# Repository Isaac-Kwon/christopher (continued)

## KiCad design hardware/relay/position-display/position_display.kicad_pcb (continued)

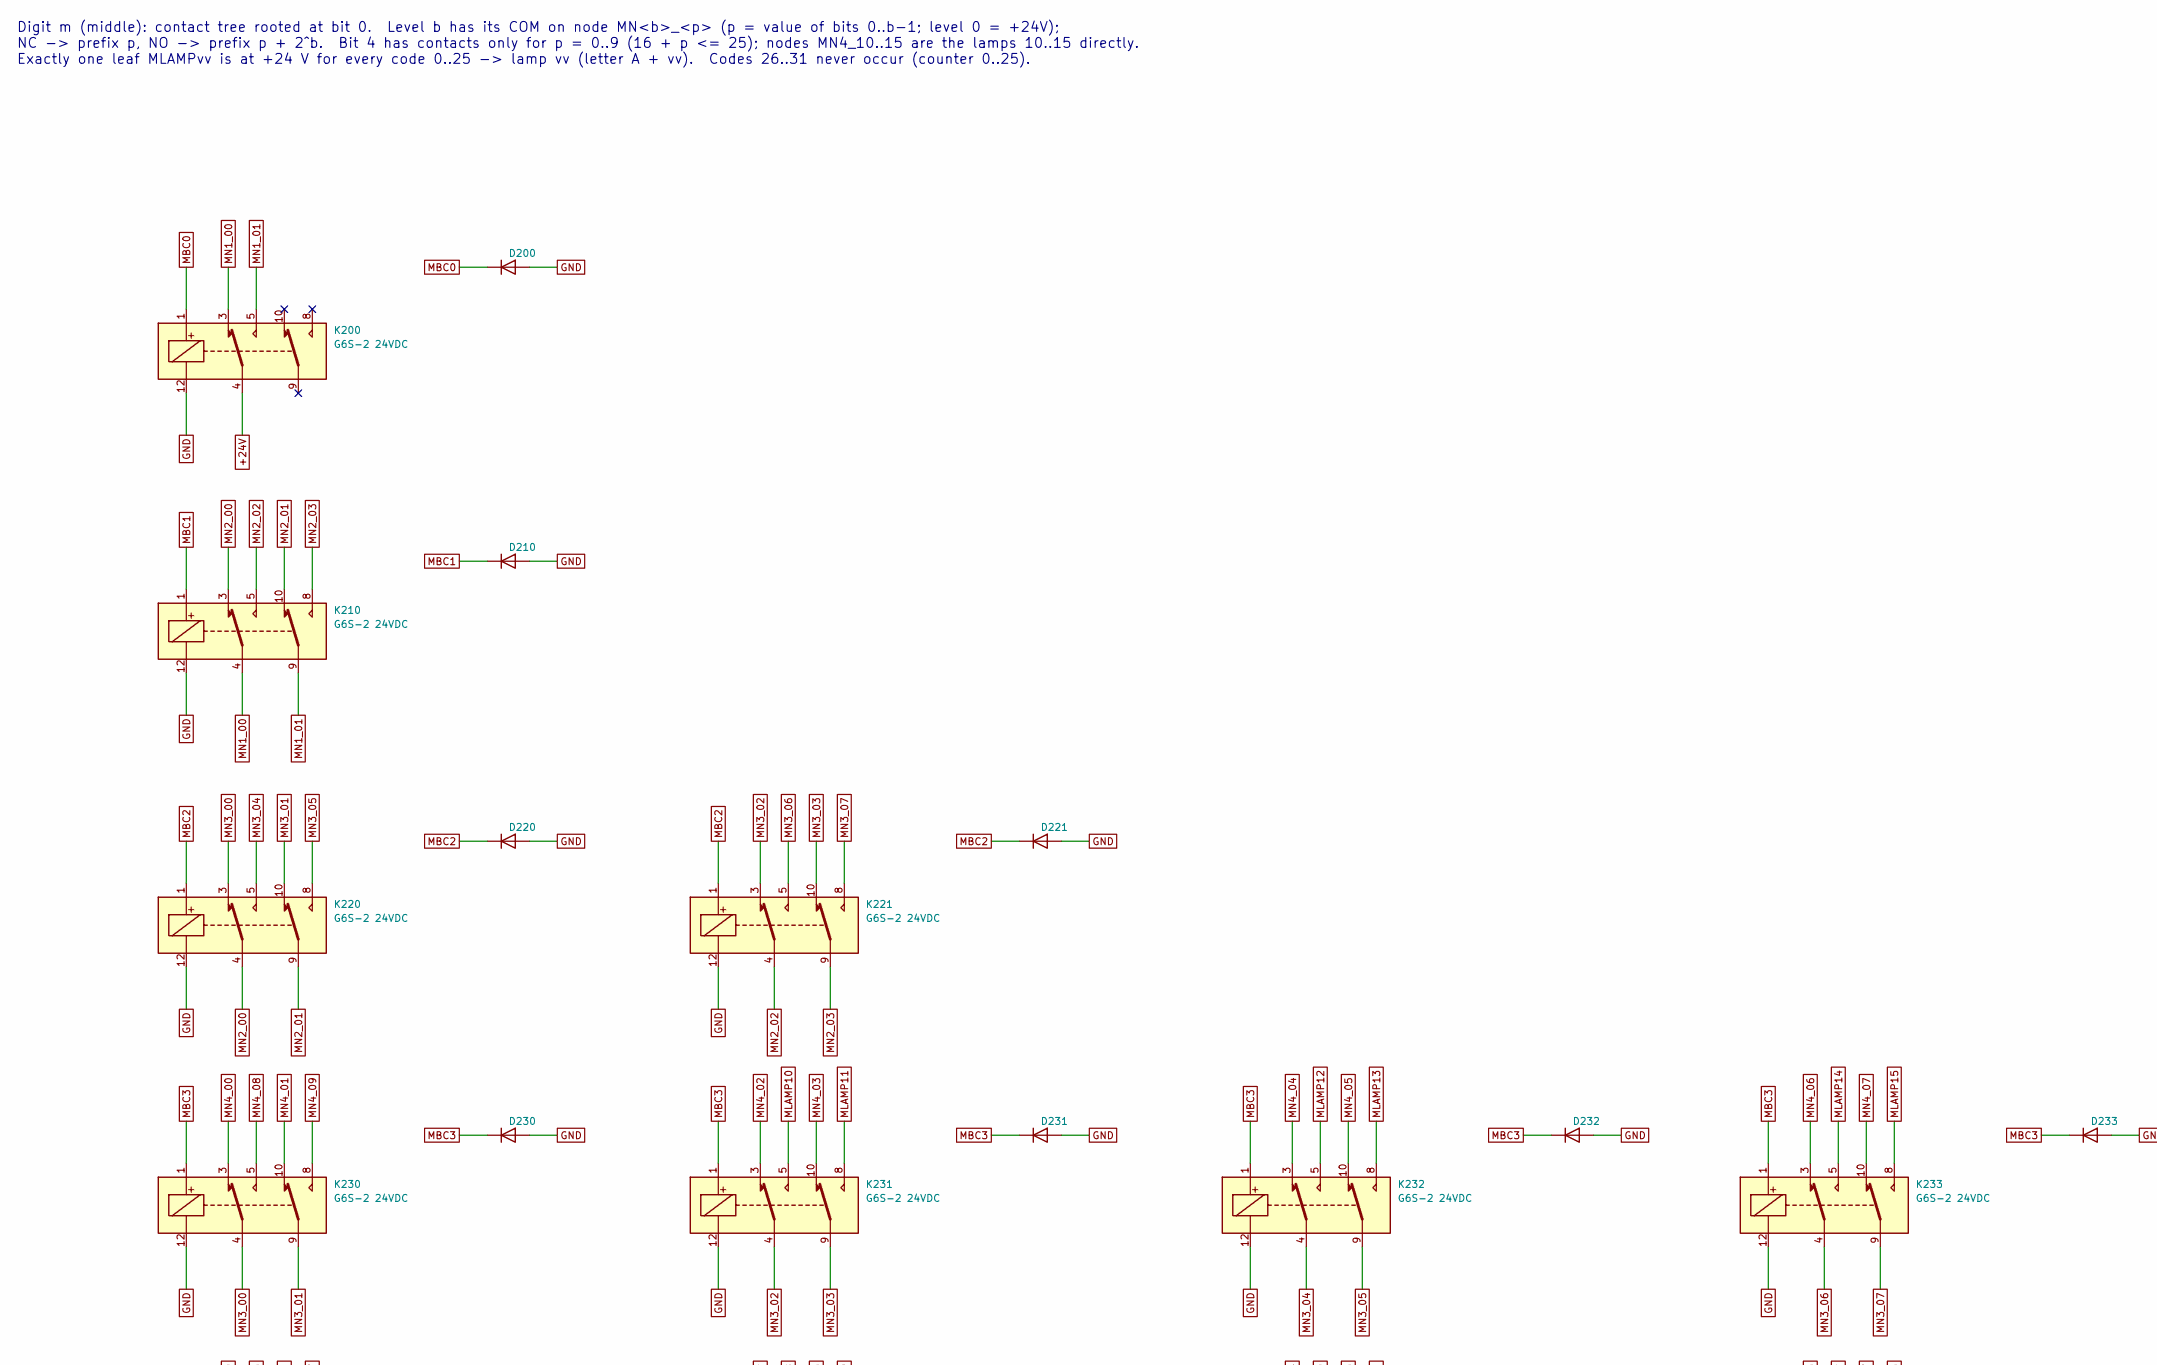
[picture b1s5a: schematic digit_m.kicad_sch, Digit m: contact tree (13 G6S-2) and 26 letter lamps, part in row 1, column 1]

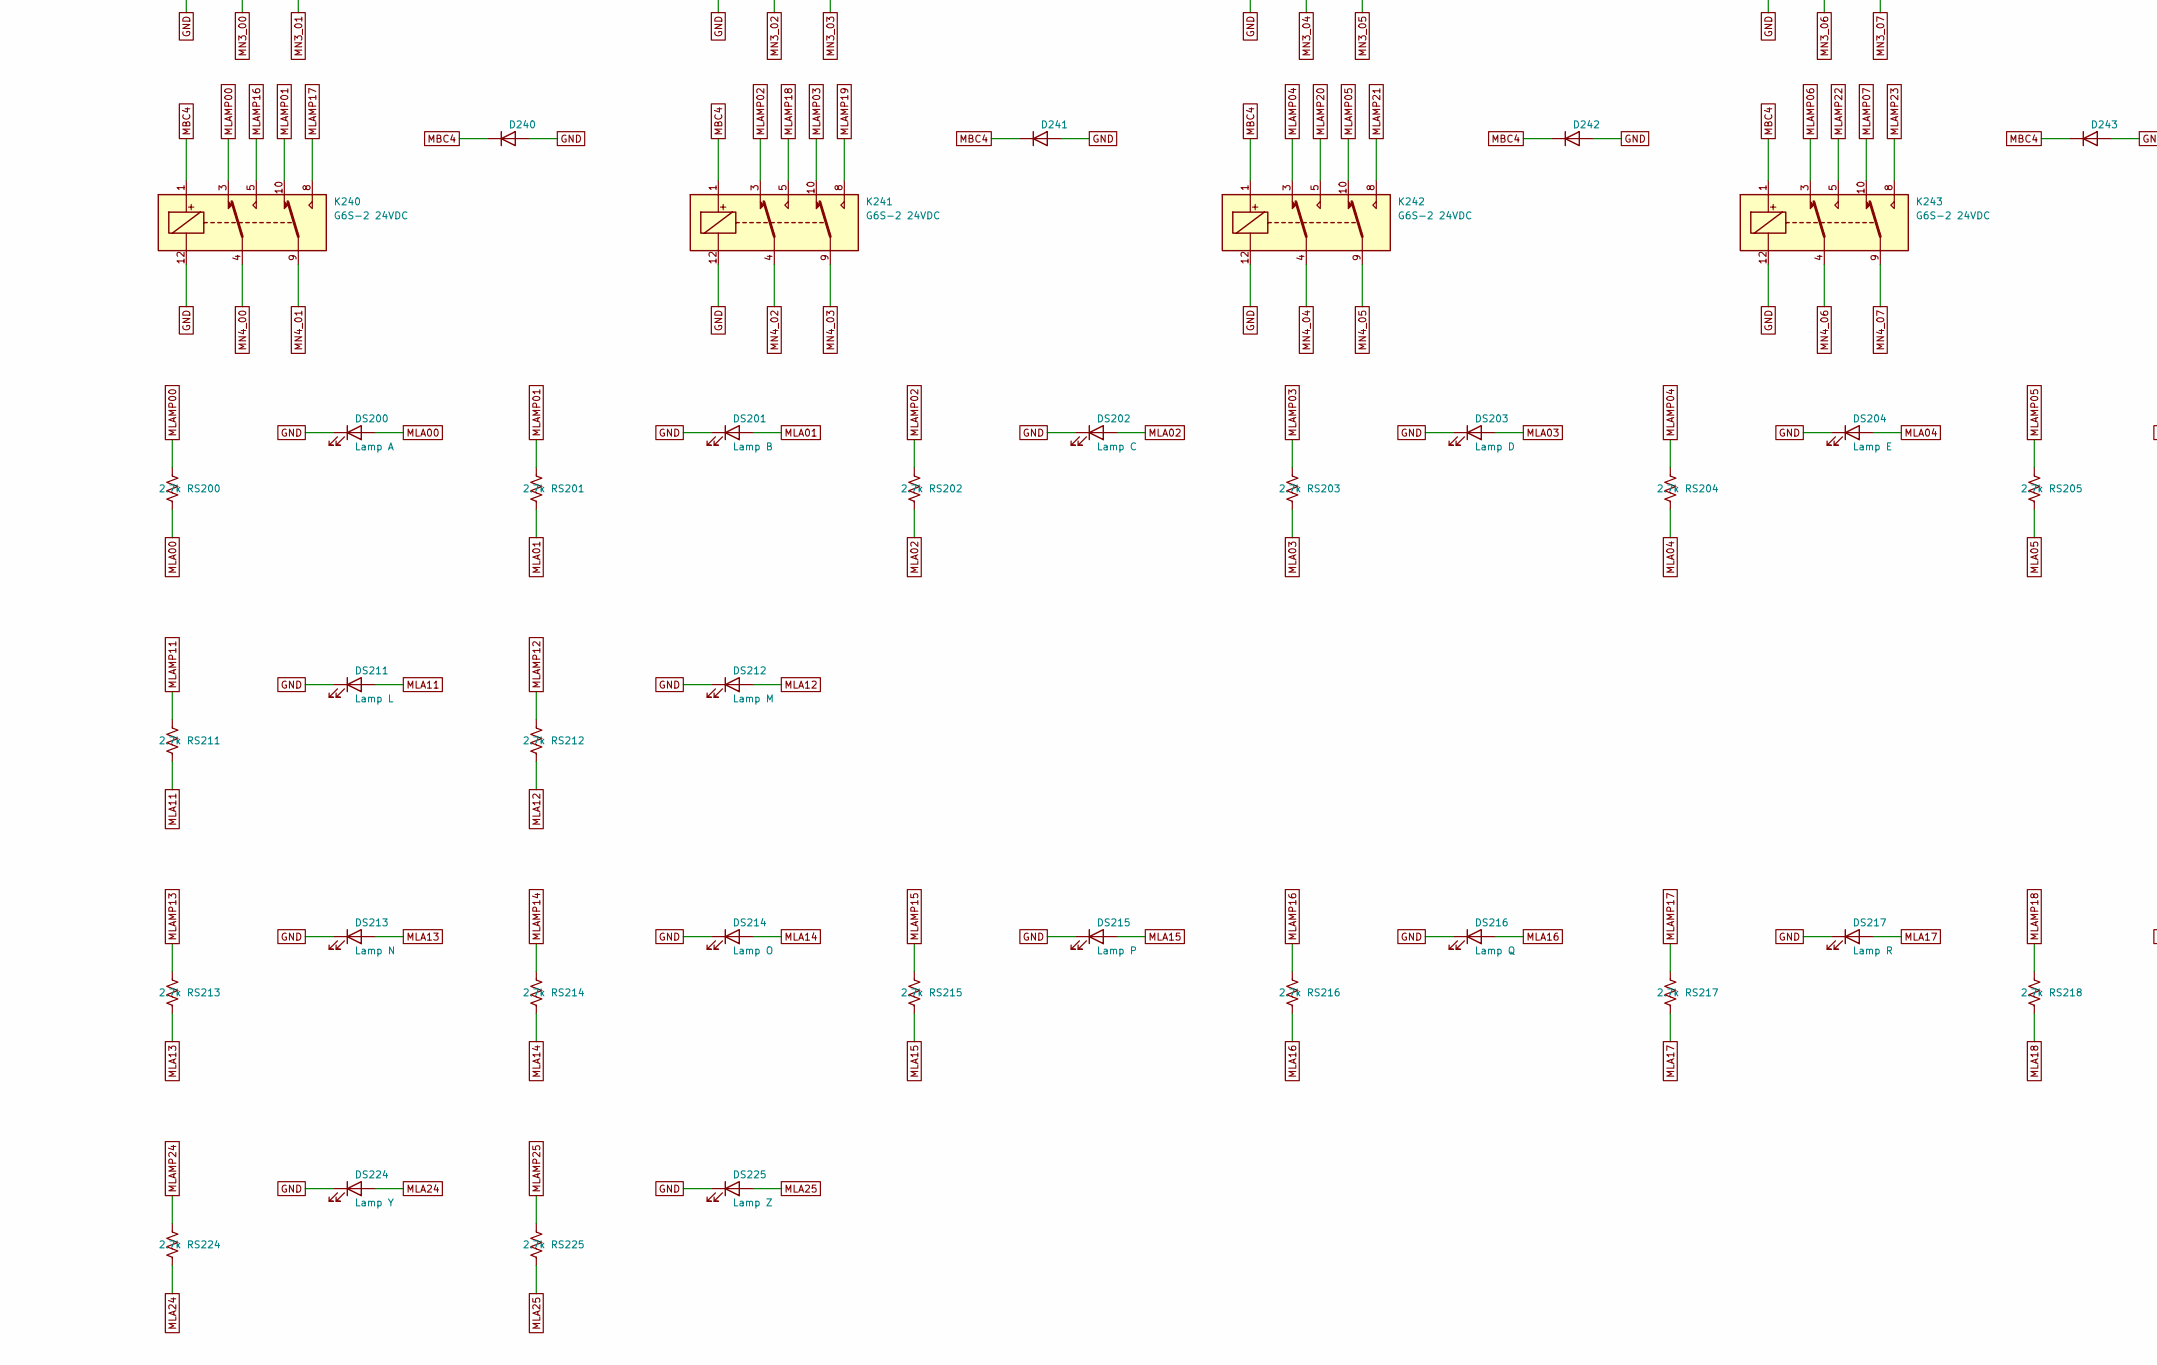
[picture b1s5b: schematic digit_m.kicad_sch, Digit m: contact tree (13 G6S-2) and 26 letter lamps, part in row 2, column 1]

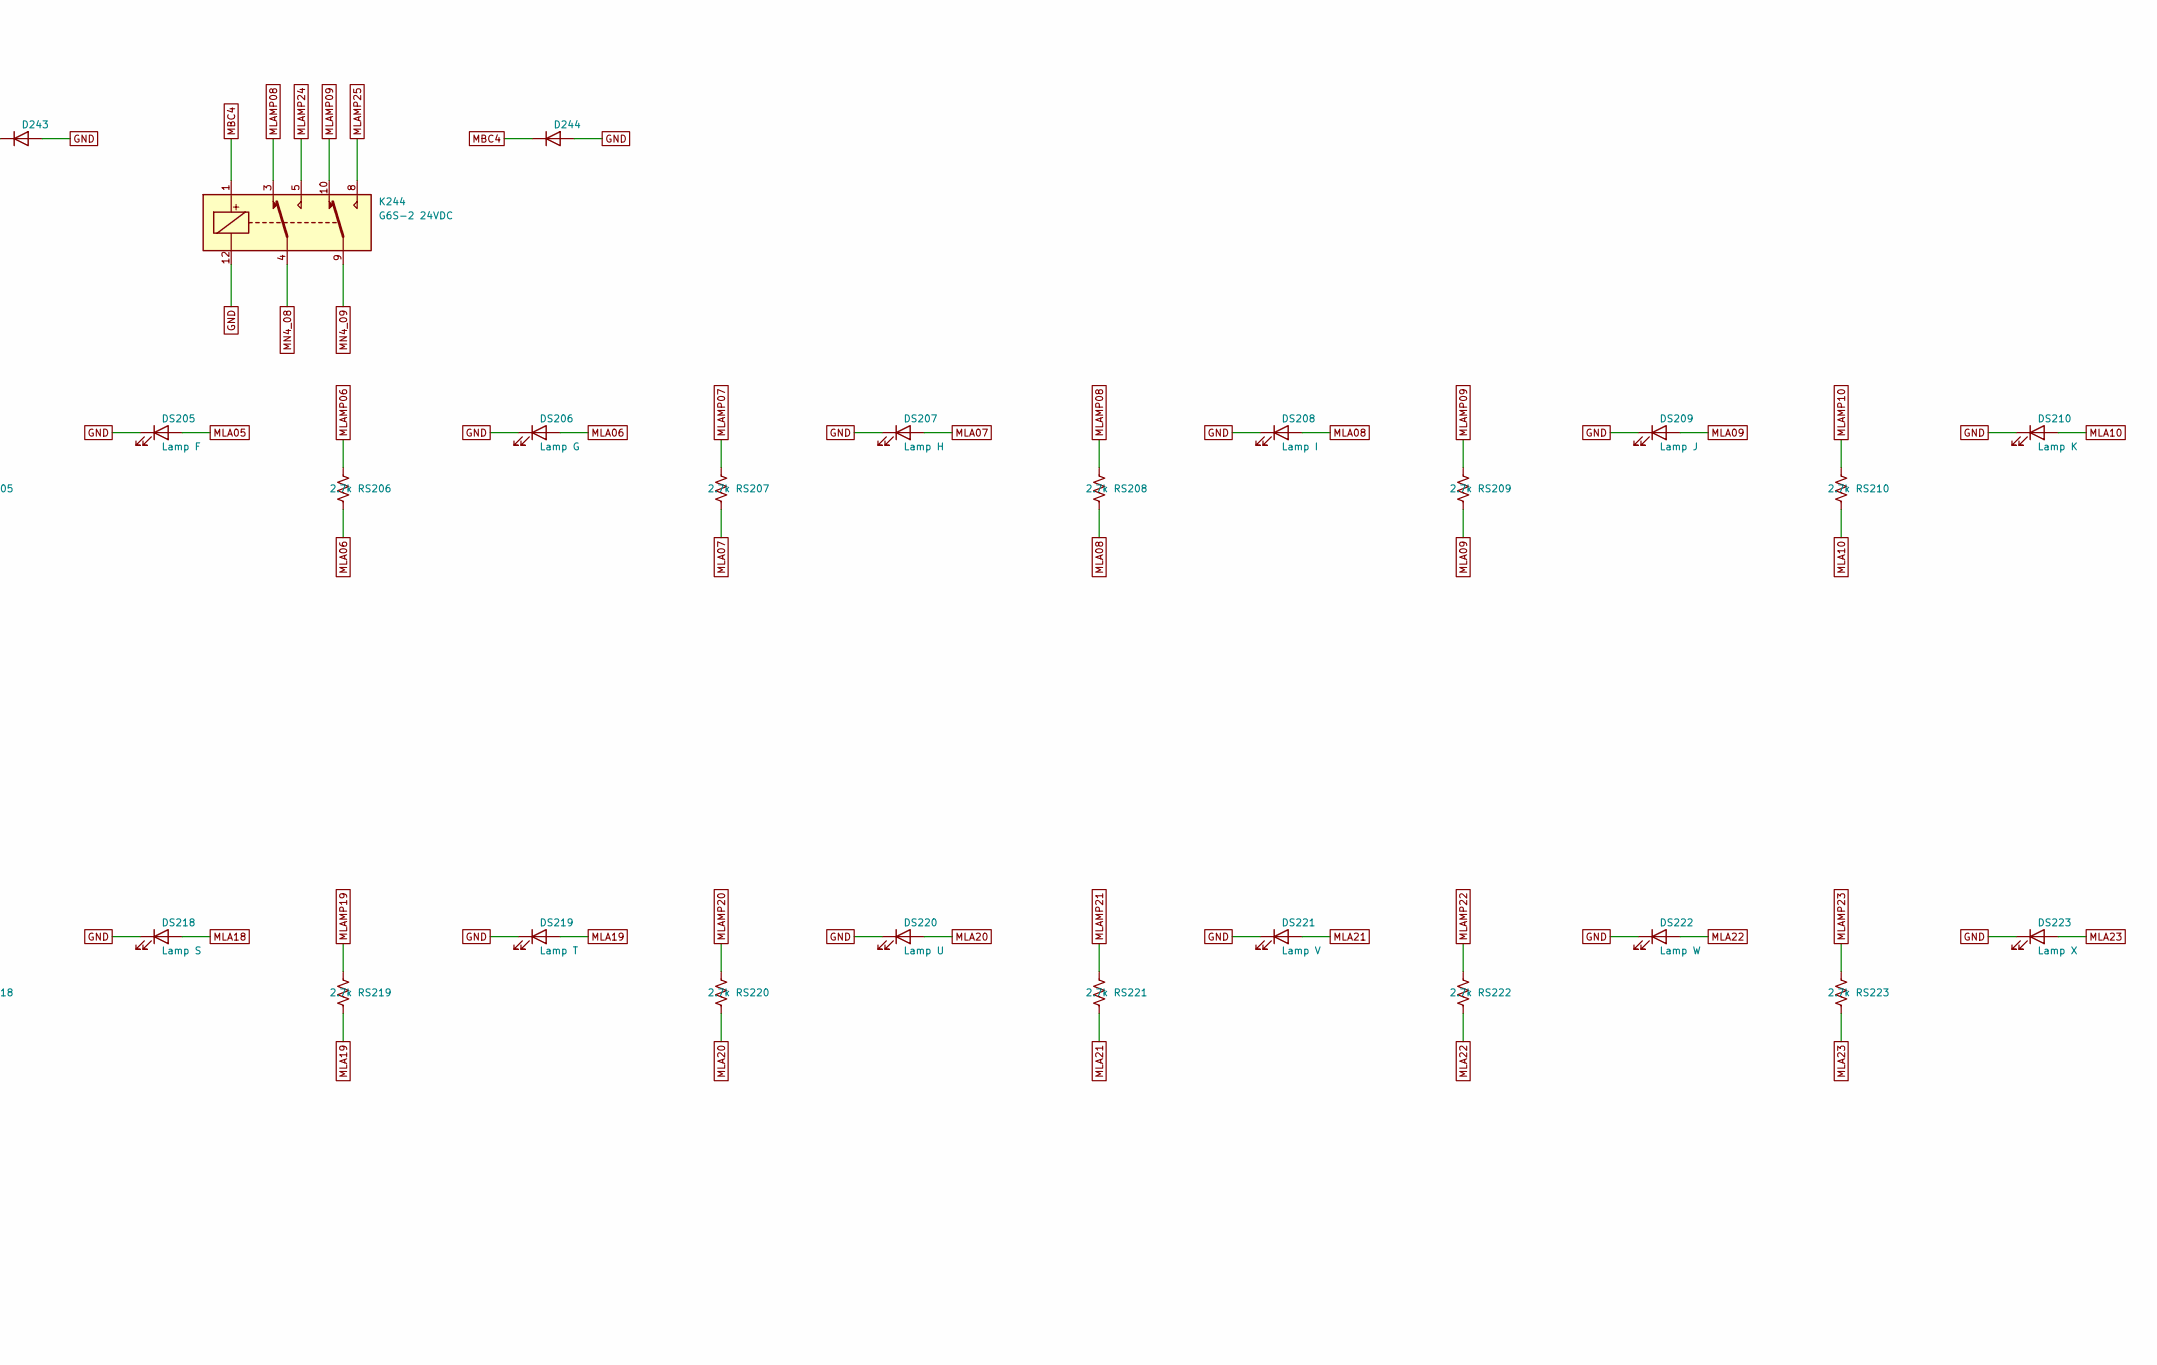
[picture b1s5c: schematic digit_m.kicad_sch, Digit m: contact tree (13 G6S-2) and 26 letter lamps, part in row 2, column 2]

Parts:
D200, D210, D220, D221, D230, D231, D232, D233, D240, D241, D242, D243, D244: 1N4148W; D_SOD-123
DS200: Lamp A; LED_D5.0mm
DS201: Lamp B; LED_D5.0mm
DS202: Lamp C; LED_D5.0mm
DS203: Lamp D; LED_D5.0mm
DS204: Lamp E; LED_D5.0mm
DS205: Lamp F; LED_D5.0mm
DS206: Lamp G; LED_D5.0mm
DS207: Lamp H; LED_D5.0mm
DS208: Lamp I; LED_D5.0mm
DS209: Lamp J; LED_D5.0mm
DS210: Lamp K; LED_D5.0mm
DS211: Lamp L; LED_D5.0mm
DS212: Lamp M; LED_D5.0mm
DS213: Lamp N; LED_D5.0mm
DS214: Lamp O; LED_D5.0mm
DS215: Lamp P; LED_D5.0mm
DS216: Lamp Q; LED_D5.0mm
DS217: Lamp R; LED_D5.0mm
DS218: Lamp S; LED_D5.0mm
DS219: Lamp T; LED_D5.0mm
DS220: Lamp U; LED_D5.0mm
DS221: Lamp V; LED_D5.0mm
DS222: Lamp W; LED_D5.0mm
DS223: Lamp X; LED_D5.0mm
DS224: Lamp Y; LED_D5.0mm
DS225: Lamp Z; LED_D5.0mm
K200, K210, K220, K221, K230, K231, K232, K233, K240, K241, K242, K243, K244: G6S-2 24VDC; Relay_DPDT_Omron_G6S-2
RS200, RS201, RS202, RS203, RS204, RS205, RS206, RS207, RS208, RS209, RS210, RS211, RS212, RS213, RS214, RS215, RS216, RS217, RS218, RS219, RS220, RS221, RS222, RS223, RS224, RS225: 2.7k; R_1206_3216Metric

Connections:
+24V: K200.4; also elsewhere on the board
GND: D200.2 (A), D210.2 (A), D220.2 (A), D221.2 (A), D230.2 (A), D231.2 (A), D232.2 (A), D233.2 (A), D240.2 (A), D241.2 (A), D242.2 (A), D243.2 (A), D244.2 (A), DS200.1 (K), DS201.1 (K), DS202.1 (K), DS203.1 (K), DS204.1 (K), DS205.1 (K), DS206.1 (K), DS207.1 (K), DS208.1 (K), DS209.1 (K), DS210.1 (K), DS211.1 (K), DS212.1 (K), DS213.1 (K), DS214.1 (K), DS215.1 (K), DS216.1 (K), DS217.1 (K), DS218.1 (K), DS219.1 (K), DS220.1 (K), DS221.1 (K), DS222.1 (K), DS223.1 (K), DS224.1 (K), DS225.1 (K), K200.12, K210.12, K220.12, K221.12, K230.12, K231.12, K232.12, K233.12, K240.12, K241.12, K242.12, K243.12, K244.12; also elsewhere on the board
MBC0: D200.1 (K), K200.1; also elsewhere on the board
MBC1: D210.1 (K), K210.1; also elsewhere on the board
MBC2: D220.1 (K), D221.1 (K), K220.1, K221.1; also elsewhere on the board
MBC3: D230.1 (K), D231.1 (K), D232.1 (K), D233.1 (K), K230.1, K231.1, K232.1, K233.1; also elsewhere on the board
MBC4: D240.1 (K), D241.1 (K), D242.1 (K), D243.1 (K), D244.1 (K), K240.1, K241.1, K242.1, K243.1, K244.1; also elsewhere on the board
MLA00: DS200.2 (A), RS200.2
MLA01: DS201.2 (A), RS201.2
MLA02: DS202.2 (A), RS202.2
MLA03: DS203.2 (A), RS203.2
MLA04: DS204.2 (A), RS204.2
MLA05: DS205.2 (A), RS205.2
MLA06: DS206.2 (A), RS206.2
MLA07: DS207.2 (A), RS207.2
MLA08: DS208.2 (A), RS208.2
MLA09: DS209.2 (A), RS209.2
MLA10: DS210.2 (A), RS210.2
MLA11: DS211.2 (A), RS211.2
MLA12: DS212.2 (A), RS212.2
MLA13: DS213.2 (A), RS213.2
MLA14: DS214.2 (A), RS214.2
MLA15: DS215.2 (A), RS215.2
MLA16: DS216.2 (A), RS216.2
MLA17: DS217.2 (A), RS217.2
MLA18: DS218.2 (A), RS218.2
MLA19: DS219.2 (A), RS219.2
MLA20: DS220.2 (A), RS220.2
MLA21: DS221.2 (A), RS221.2
MLA22: DS222.2 (A), RS222.2
MLA23: DS223.2 (A), RS223.2
MLA24: DS224.2 (A), RS224.2
MLA25: DS225.2 (A), RS225.2
MLAMP00: K240.3, RS200.1
MLAMP01: K240.10, RS201.1
MLAMP02: K241.3, RS202.1
MLAMP03: K241.10, RS203.1
MLAMP04: K242.3, RS204.1
MLAMP05: K242.10, RS205.1
MLAMP06: K243.3, RS206.1
MLAMP07: K243.10, RS207.1
MLAMP08: K244.3, RS208.1
MLAMP09: K244.10, RS209.1
MLAMP10: K231.5, RS210.1
MLAMP11: K231.8, RS211.1
MLAMP12: K232.5, RS212.1
MLAMP13: K232.8, RS213.1
MLAMP14: K233.5, RS214.1
MLAMP15: K233.8, RS215.1
MLAMP16: K240.5, RS216.1
MLAMP17: K240.8, RS217.1
MLAMP18: K241.5, RS218.1
MLAMP19: K241.8, RS219.1
MLAMP20: K242.5, RS220.1
MLAMP21: K242.8, RS221.1
MLAMP22: K243.5, RS222.1
MLAMP23: K243.8, RS223.1
MLAMP24: K244.5, RS224.1
MLAMP25: K244.8, RS225.1
MN1_00: K200.3, K210.4
MN1_01: K200.5, K210.9
MN2_00: K210.3, K220.4
MN2_01: K210.10, K220.9
MN2_02: K210.5, K221.4
MN2_03: K210.8, K221.9
MN3_00: K220.3, K230.4
MN3_01: K220.10, K230.9
MN3_02: K221.3, K231.4
MN3_03: K221.10, K231.9
MN3_04: K220.5, K232.4
MN3_05: K220.8, K232.9
MN3_06: K221.5, K233.4
MN3_07: K221.8, K233.9
MN4_00: K230.3, K240.4
MN4_01: K230.10, K240.9
MN4_02: K231.3, K241.4
MN4_03: K231.10, K241.9
MN4_04: K232.3, K242.4
MN4_05: K232.10, K242.9
MN4_06: K233.3, K243.4
MN4_07: K233.10, K243.9
MN4_08: K230.5, K244.4
MN4_09: K230.8, K244.9

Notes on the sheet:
Digit m (middle): contact tree rooted at bit 0. Level b has its COM on node MN<b>_<p> (p = value of bits 0..b-1; level 0 = +24V); NC -> prefix p, NO -> prefix p + 2^b. Bit 4 has contacts only for p = 0..9 (16 + p <= 25); nodes MN4_10..15 are the lamps 10..15 directly. Exactly one leaf MLAMPvv is at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
